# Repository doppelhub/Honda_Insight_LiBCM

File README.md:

# Honda_Insight_LiBCM
Replacement BCM for G1 Honda Insight Lithium Conversion
Licensed under Creative Commons - Attribution - ShareAlike 3.0
Project created and maintained by insightcentral.net user 'mudder' (a.k.a. John Sullivan).

<<<<<<< HEAD
LiBCM is a replacement computer that allows the G1 Honda Insight (2000-2006) to safely use modern lithium traction batteries.
=======
This is Natalya's fork repository for her branch on the LiBCM Project, which is created by insightcentral.net user 'mudder' (a.k.a. John Sullivan).
>>>>>>> f23abbbc6b13445ddd2d59ccdc4642e3edeb463f

LiBCM replaces the OEM Battery Control Module (BCM).  LiBCM is presently offered as two different 'Kits':
-'5AhG3 LiBCM Kit' uses 12S & 18S lithium battery modules from various modern Honda hybrids, or;
-'47Ah LiBCM Kit' uses 12S Samsung SDI lithium battery modules

<<<<<<< HEAD
While other lithium battery types are theoretically supported, integrating them with LiBCM is beyond the design goals for this project.  A few customers are using non-supported modules, but it requires custom BMS harnesses and also cell discharge curve characterization to create a Voc->SoC lookup table.

LiBCM officially supports the following lithium configurations:
-'5AhG3' - 48S ONLY, or;
-'47Ah'- either 48S or 60S.

NO OTHER CONFIGURATION is officially supported.  While the PCB's onboard BMS supports anywhere from 6S to 60S, you're on your own (firmware-wise) if you want to run anything besides 48S.  Future firmware updates might allow 54S and/or 60S support. 

See linsight.org for more information.
=======
LiBCM officially supports either 42S or 48S lithium configurations.  NO OTHER CONFIGURATION is officially supported.  While the PCB's onboard BMS supports anywhere from 6S to 60S - and also safely supports up to 84S using external modules (via an isoSPI interface), you're on your own (firmware-wise) if you want to run anything beyond 42S or 48S.
>>>>>>> f23abbbc6b13445ddd2d59ccdc4642e3edeb463f

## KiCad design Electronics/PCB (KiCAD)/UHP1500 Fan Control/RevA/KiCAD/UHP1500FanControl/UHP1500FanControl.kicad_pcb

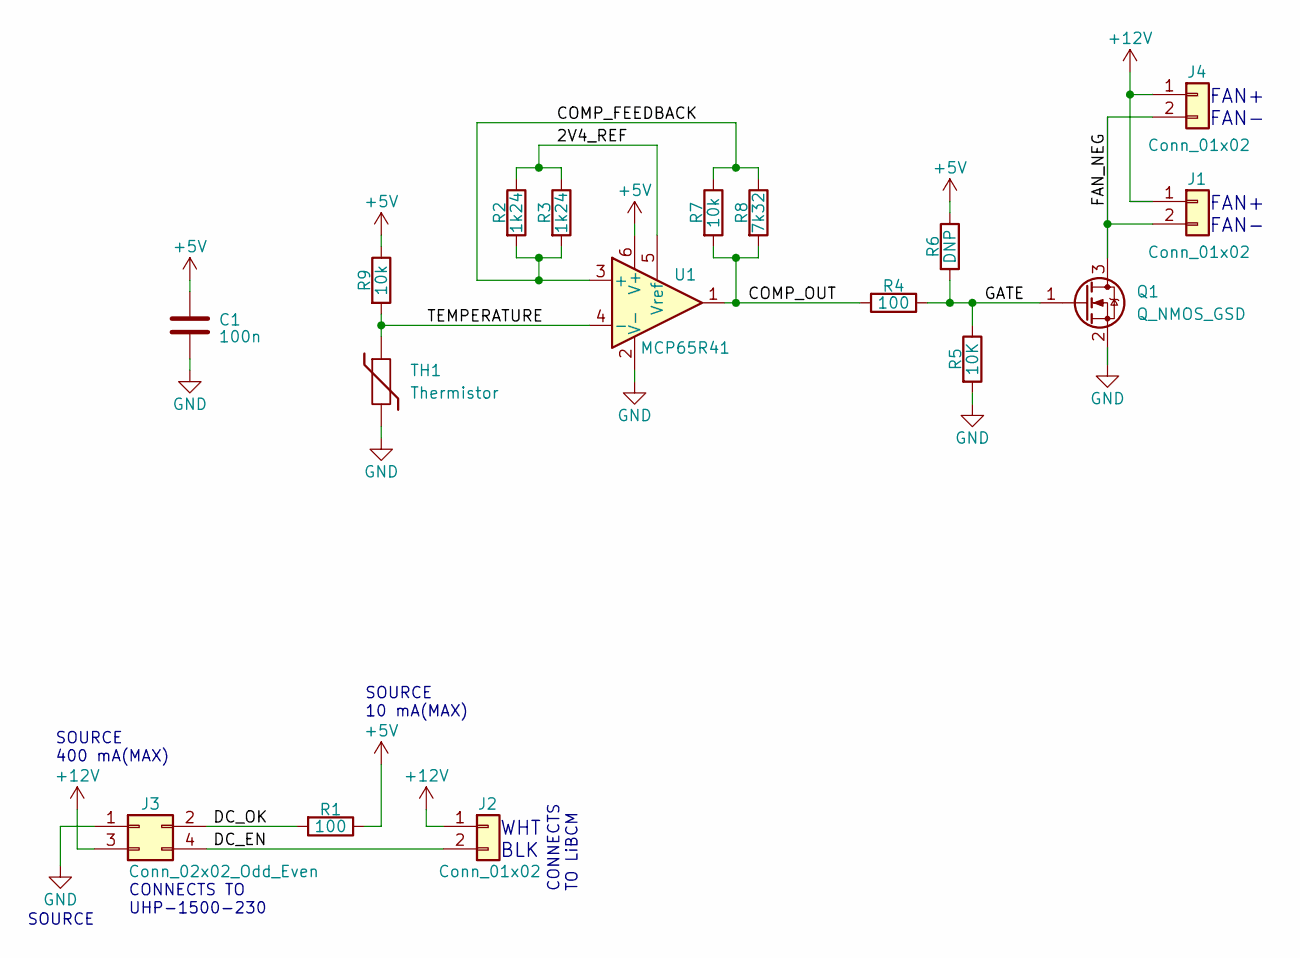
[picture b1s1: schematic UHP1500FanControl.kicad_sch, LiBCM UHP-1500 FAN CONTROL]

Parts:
C1: 100n; C_0805_2012Metric
J1, J2, J4: Conn_01x02; DIP-4_W8.89mm_SMDSocket_LongPads
J3: Conn_02x02_Odd_Even; PinHeader_2x02_P2.54mm_Vertical
Q1: Q_NMOS_GSD; SOT-23
R1, R4: 100; R_0805_2012Metric
R2, R3: 1k24; R_0805_2012Metric
R5: 10K; R_0805_2012Metric
R6: DNP; R_0805_2012Metric
R7, R9: 10k; R_0805_2012Metric
R8: 7k32; R_0805_2012Metric
TH1: Thermistor; R_0805_2012Metric
U1: MCP65R41; SOT-23-6

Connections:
+5V: C1.1, R1.1, R6.1, R9.1, U1.6 (V+)
+12V: J1.1, J2.1, J3.3, J4.1
/2V4_REF: R2.1, R3.1, U1.5 (Vref)
/COMP_FEEDBACK: R2.2, R3.2, R7.1, R8.1, U1.3 (+)
/COMP_OUT: R4.2, R7.2, R8.2, U1.1
/DC_EN: J2.2, J3.4
/DC_OK: J3.2, R1.2
/FAN_NEG: J1.2, J4.2, Q1.3 (D)
/GATE: Q1.1 (G), R4.1, R5.1, R6.2
/TEMPERATURE: R9.2, TH1.1, U1.4 (-)
GND: C1.2, J3.1, Q1.2 (S), R5.2, TH1.2, U1.2 (V-)

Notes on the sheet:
SOURCE 10 mA(MAX)
FAN+ FAN-
WHT BLK
CONNECTS TO LiBCM
SOURCE
CONNECTS TO UHP-1500-230
SOURCE 400 mA(MAX)

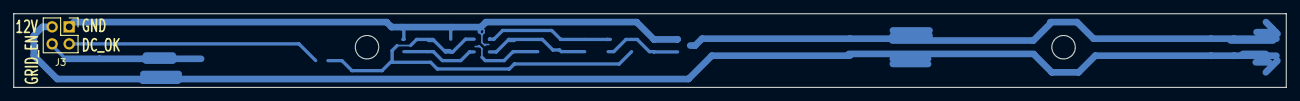
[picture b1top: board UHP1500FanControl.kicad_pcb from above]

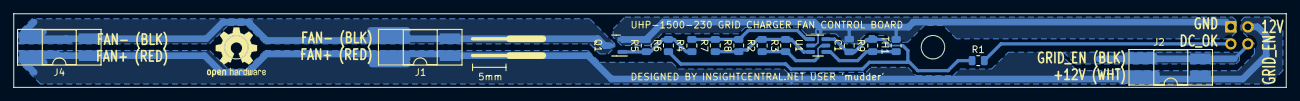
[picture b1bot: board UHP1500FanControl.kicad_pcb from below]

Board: 2 copper layers, 190.0 x 11.0 mm, 17 parts (16 on the bottom side), 11 nets.

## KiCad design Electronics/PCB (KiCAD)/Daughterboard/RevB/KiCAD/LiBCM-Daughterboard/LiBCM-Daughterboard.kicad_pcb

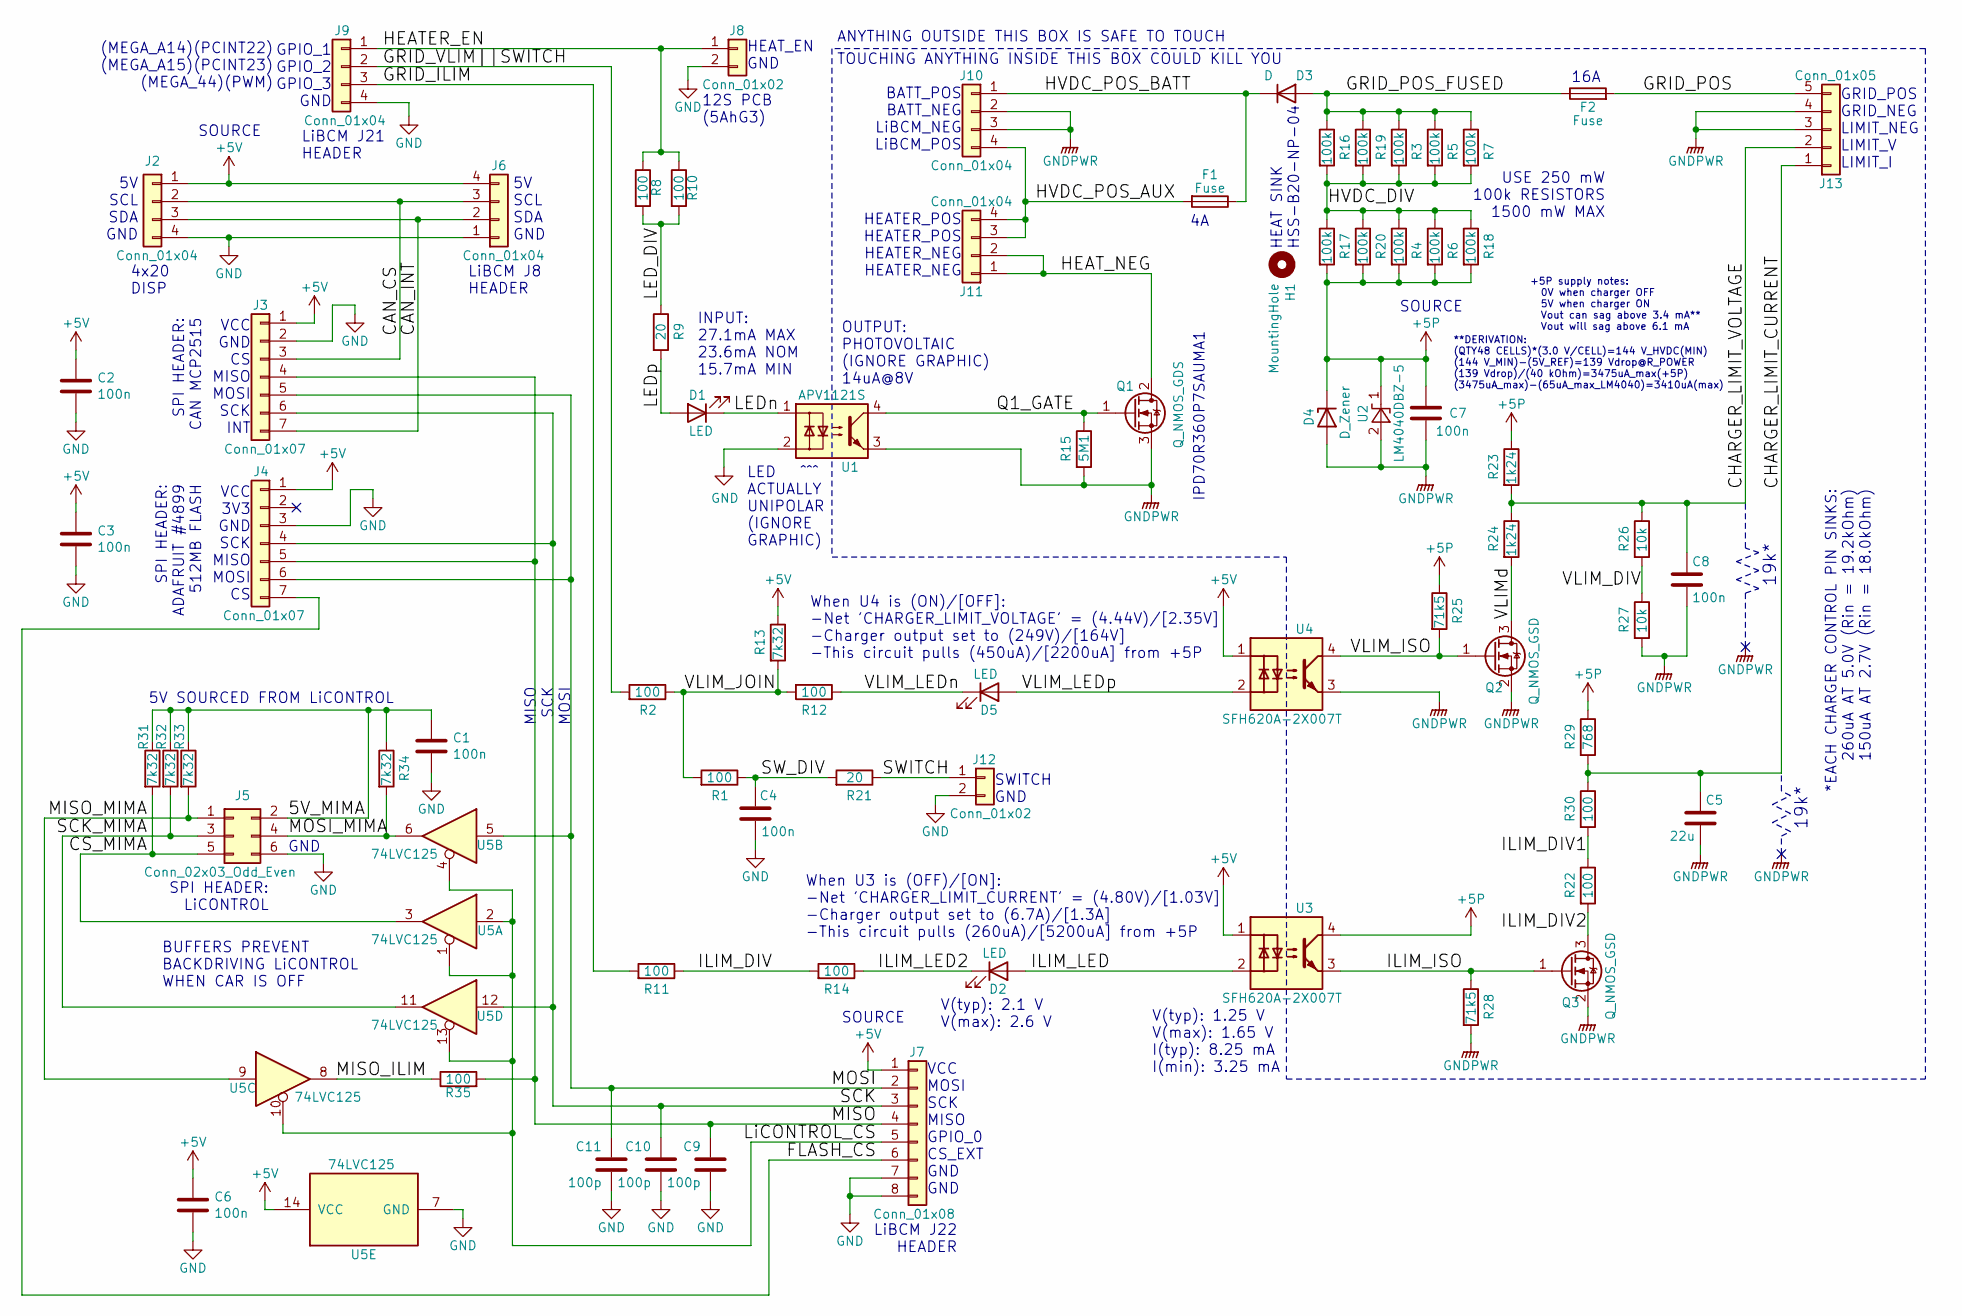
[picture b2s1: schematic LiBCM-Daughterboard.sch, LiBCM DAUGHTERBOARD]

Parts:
C1, C2, C3, C4, C6, C7, C8: 100n; C_0805_2012Metric
C5: 22u; C_1210_3225Metric
C9, C10, C11: 100p; C_0805_2012Metric
D1, D2, D5: LED; LED_0805_2012Metric
D3: D; TO-220-2_Horizontal_TabDown
D4: D_Zener; D_SOD-123
F1, F2: Fuse; Fuseholder_Cylinder-5x20mm_Schurter_0031_8201_Horizontal_Op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
H1: MountingHole; MountingHole_3.2mm_M3
J2, J6, J9: Conn_01x04; PinHeader_1x04_P2.54mm_Vertical
J3, J4: Conn_01x07; PinHeader_1x07_P2.54mm_Vertical
J5: Conn_02x03_Odd_Even; PinHeader_2x03_P2.54mm_Vertical
J7: Conn_01x08; PinHeader_1x08_P2.54mm_Vertical
J8, J12: Conn_01x02; PinHeader_1x02_P2.54mm_Vertical
J10, J11: Conn_01x04; PhoenixContact_MCV_1,5_4-G-3.5_1x04_P3.50mm_Vertical
J13: Conn_01x05; PhoenixContact_MCV_1,5_5-G-3.5_1x05_P3.50mm_Vertical
Q1: Q_NMOS_GDS; TO-252-3_TabPin2
Q2, Q3: Q_NMOS_GSD; SOT-23
R1, R2, R8, R10, R11, R12, R14, R22, R30, R35: 100; R_0805_2012Metric
R3, R4, R5, R6, R7, R16, R17, R18, R19, R20: 100k; R_0805_2012Metric
R9, R21: 20; R_0805_2012Metric
R13, R31, R32, R33, R34: 7k32; R_0805_2012Metric
R15: 5M1; R_1206_3216Metric
R23, R24: 1k24; R_0805_2012Metric
R25, R28: 71k5; R_0805_2012Metric
R26, R27: 10k; R_0805_2012Metric
R29: 768; R_0805_2012Metric
U1: APV1121S; SOP-4_3.8x4.1mm_P2.54mm
U2: LM4040DBZ-5; SOT-23
U3, U4: SFH620A-2X007T; SMDIP-4_W9.53mm_Clearance8mm
U5: 74LVC125; SO-14_3.9x8.65mm_P1.27mm

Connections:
+5P: C7.1, D4.1 (K), R4.2, R6.2, R17.2, R18.2, R20.2, R23.1, R25.1, R29.1, U2.1 (K), U3.4
+5V: C2.1, C3.1, C6.1, J2.1, J3.1, J4.1, J6.4, J7.1, R13.1, U3.1, U4.1, U5.14 (VCC)
/5V_MIMA: C1.1, J5.2, R31.1, R32.1, R33.1, R34.1
/CAN_CS: J2.2, J3.3, J6.3
/CAN_INT: J2.3, J3.7, J6.2
/CHARGER_LIMIT_CURRENT: C5.1, J13.1, R29.2, R30.1
/CHARGER_LIMIT_VOLTAGE: C8.1, J13.2, R23.2, R24.1, R26.1
/CS_MIMA: J5.5, R31.2, U5.3
/FLASH_CS: J4.7, J7.6
/GRID_ILIM: J9.3, R11.2
/GRID_POS: F2.2, J13.5
/GRID_POS_FUSED: D3.2 (A), F2.1, R3.1, R5.1, R7.1, R16.1, R19.1
/GRID_VLIM||SWITCH: J9.2, R2.2
/HEATER_EN: J8.1, J9.1, R8.1, R10.1
/HEAT_NEG: J11.1, J11.2, Q1.2 (D)
/HVDC_DIV: R3.2, R4.1, R5.2, R6.1, R7.2, R16.2, R17.1, R18.1, R19.2, R20.1
/HVDC_POS_AUX: F1.2, J10.4, J11.3, J11.4
/HVDC_POS_BATT: D3.1 (K), F1.1, J10.1
/ILIM_DIV1: R22.1, R30.2
/ILIM_DIV2: Q3.3 (D), R22.2
/ILIM_ISO: Q3.1 (G), R28.1, U3.3
/ILIM_LED_1: R11.1, R14.2
/ILIM_LED_2: D2.1 (K), R14.1; also elsewhere on the board
/ILIM_LED_3: D2.2 (A), U3.2; also elsewhere on the board
/LED_DIV: R8.2, R9.1, R10.2
/LEDn: D1.1 (K), U1.1
/LEDp: D1.2 (A), R9.2
/LiCONTROL_CS: J7.5, U5.1, U5.2, U5.4, U5.10, U5.13
/MISO: C9.1, J3.4, J4.5, J7.4, R35.2
/MISO_ILIM: R35.1, U5.8
/MISO_MIMA: J5.1, R33.2, U5.9
/MOSI: C11.1, J3.5, J4.6, J7.2, U5.5
/MOSI_MIMA: J5.4, R34.2, U5.6
/Q1_GATE: Q1.1 (G), R15.1, U1.4
/SCK: C10.1, J3.6, J4.4, J7.3, U5.12
/SCK_MIMA: J5.3, R32.2, U5.11
/SWITCH: J12.1, R21.1
/SW_DIV: C4.1, R1.1, R21.2
/VLIM_DIV: R26.2, R27.1
/VLIM_ISO: Q2.1 (G), R25.2, U4.4
/VLIM_JOIN: R1.2, R2.1, R12.2, R13.2
/VLIM_LEDn: D5.1 (K), R12.1
/VLIM_LEDp: D5.2 (A), U4.2
/VLIMd: Q2.3 (D), R24.2
GND: C1.2, C2.2, C3.2, C4.2, C6.2, C9.2, C10.2, C11.2, J2.4, J3.2, J4.3, J5.6, J6.1, J7.7, J7.8, J8.2, J9.4, J12.2, U1.2, U5.7 (GND)
GNDPWR: C5.2, C7.2, C8.2, D4.2 (A), J10.2, J10.3, J13.3, J13.4, Q1.3 (S), Q2.2 (S), Q3.2 (S), R15.2, R27.2, R28.2, U1.3, U2.2 (A), U4.3

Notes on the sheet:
GPIO_1 GPIO_2 GPIO_3 GND
SPI HEADER: CAN MCP2515
OUTPUT: PHOTOVOLTAIC (IGNORE GRAPHIC) 14uA@8V
LED ^^^ ACTUALLY UNIPOLAR (IGNORE GRAPHIC)
IPD70R360P7SAUMA1
LiBCM J21 HEADER
HEATER_POS HEATER_POS HEATER_NEG HEATER_NEG
(MEGA_A14)(PCINT22) (MEGA_A15)(PCINT23) (MEGA_44)(PWM)
SPI HEADER: ADAFRUIT #4899 512MB FLASH
VCC 3V3 GND SCK MISO MOSI CS
VCC GND CS MISO MOSI SCK INT
LiBCM J22 HEADER
VCC MOSI SCK MISO GPIO_0 CS_EXT GND GND
16A
*EACH CHARGER CONTROL PIN SINKS: 260uA AT 5.0V (Rin = 19.2kOhm) 150uA AT 2.7V (Rin = 18.0kOhm)
GRID_POS GRID_NEG LIMIT_NEG LIMIT_V LIMIT_I
BATT_POS BATT_NEG LiBCM_NEG LiBCM_POS
TOUCHING ANYTHING INSIDE THIS BOX COULD KILL YOU
ANYTHING OUTSIDE THIS BOX IS SAFE TO TOUCH
INPUT: 27.1mA MAX 23.6mA NOM 15.7mA MIN
5V SCL SDA GND
LiBCM J8 HEADER
4x20 DISP
HEAT SINK HSS-B20-NP-04
SOURCE
V(typ): 2.1 V V(max): 2.6 V
V(typ): 1.25 V V(max): 1.65 V I(typ): 8.25 mA I(min): 3.25 mA
SPI HEADER: LiCONTROL
MISO SCK MOSI
12S PCB (5AhG3)
HEAT_EN GND
19k*
When U4 is (ON)/[OFF]: -Net 'CHARGER_LIMIT_VOLTAGE' = (4.44V)/[2.35V] -Charger output set to (249V)/[164V] -This circuit pulls (450uA)/[2200uA] from +5P
SWITCH GND
When U3 is (OFF)/[ON]: -Net 'CHARGER_LIMIT_CURRENT' = (4.80V)/[1.03V] -Charger output set to (6.7A)/[1.3A] -This circuit pulls (260uA)/[5200uA] from +5P
USE 250 mW 100k RESISTORS 1500 mW MAX
+5P supply notes: 0V when charger OFF 5V when charger ON Vout can sag above 3.4 mA** Vout will sag above 6.1 mA
**DERIVATION: (QTY48 CELLS)*(3.0 V/CELL)=144 V_HVDC(MIN) (144 V_MIN)-(5V_REF)=139 Vdrop@R_POWER (139 Vdrop)/(40 kOhm)=3475uA_max(+5P) (3475uA_max)-(65uA_max_LM4040)=3410uA(max)
GND
BUFFERS PREVENT BACKDRIVING LiCONTROL WHEN CAR IS OFF

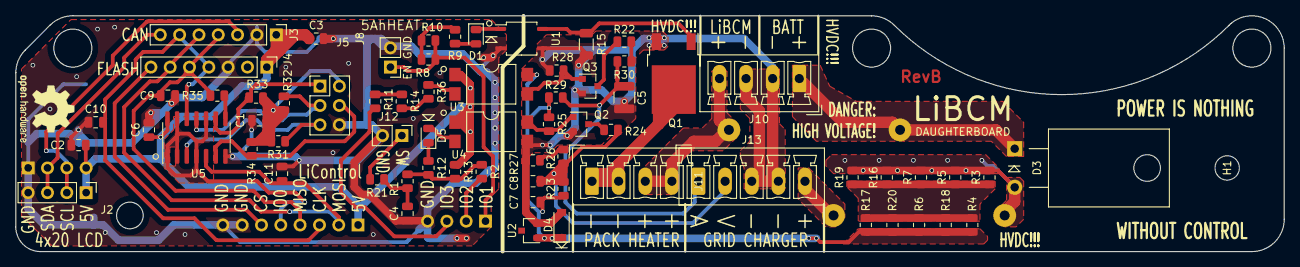
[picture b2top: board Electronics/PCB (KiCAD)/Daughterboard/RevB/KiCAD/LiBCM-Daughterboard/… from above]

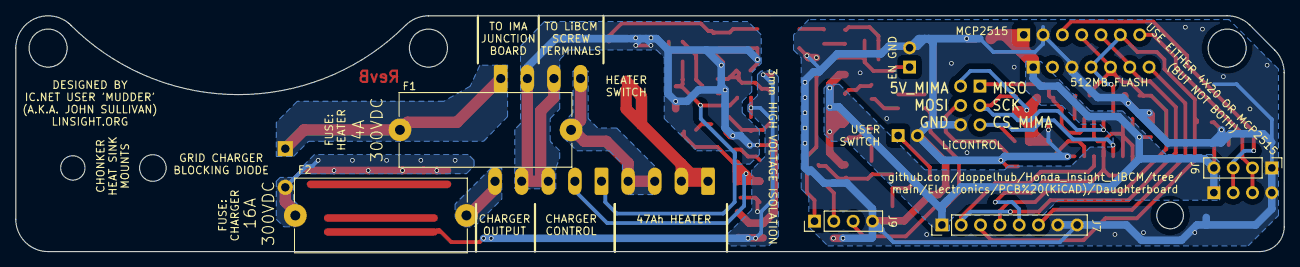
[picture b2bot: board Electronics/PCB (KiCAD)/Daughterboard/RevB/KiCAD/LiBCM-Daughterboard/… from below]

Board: 4 copper layers, 166.8 x 31.0 mm, 74 parts (5 on the bottom side), 46 nets.

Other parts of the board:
R36: 100; R_0805_2012Metric

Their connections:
/ILIM_LED_2: R36.2; also elsewhere on the board
/ILIM_LED_3: R36.1; also elsewhere on the board

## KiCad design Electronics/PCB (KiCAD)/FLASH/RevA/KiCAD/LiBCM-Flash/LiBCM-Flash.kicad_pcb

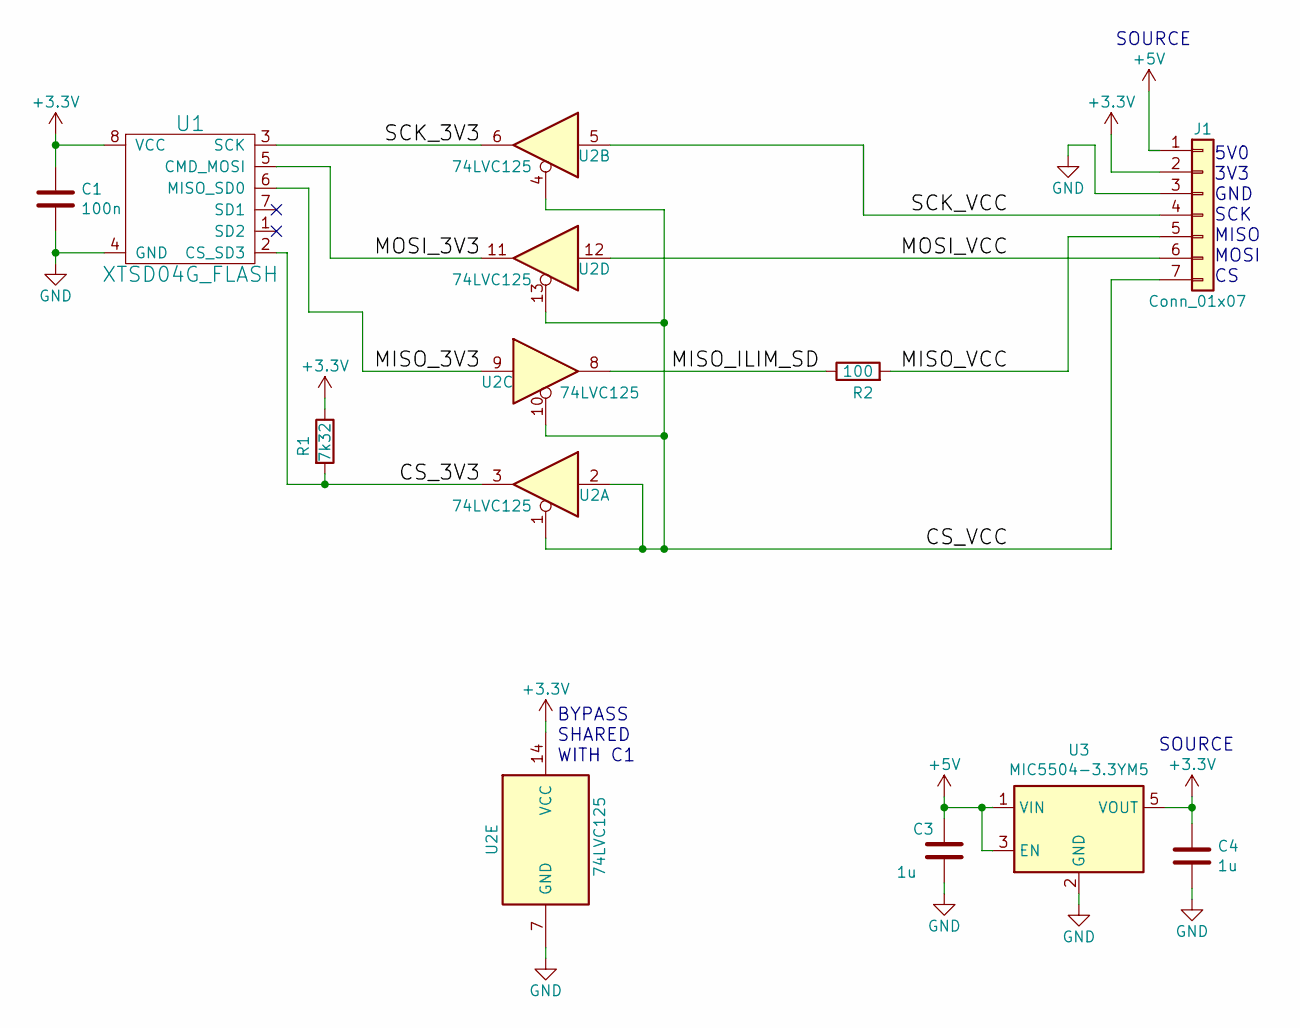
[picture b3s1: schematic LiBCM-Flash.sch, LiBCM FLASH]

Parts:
C1: 100n; C_0805_2012Metric
C3, C4: 1u; C_0805_2012Metric
J1: Conn_01x07; PinHeader_1x07_P2.54mm_Vertical
R1: 7k32; R_0805_2012Metric
R2: 100; R_0805_2012Metric
U1: XTSD04G_FLASH; NXP_LGA-8_3x5mm_P1.25mm_H1.2mm
U2: 74LVC125; SO-14_3.9x8.65mm_P1.27mm
U3: MIC5504-3.3YM5; SOT-23-5

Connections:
+3V3: C1.1, C4.1, J1.2, R1.1, U1.8 (VCC), U2.14 (VCC), U3.5 (VOUT)
+5V: C3.1, J1.1, U3.1 (VIN), U3.3 (EN)
/CS_3V3: R1.2, U1.2 (CS_SD3), U2.3
/CS_VCC: J1.7, U2.1, U2.2, U2.4, U2.10, U2.13
/MISO_3V3: U1.6 (MISO_SD0), U2.9
/MISO_ILIM_SD: R2.1, U2.8
/MISO_VCC: J1.5, R2.2
/MOSI_3V3: U1.5 (CMD_MOSI), U2.11
/MOSI_VCC: J1.6, U2.12
/SCK_3V3: U1.3 (SCK), U2.6
/SCK_VCC: J1.4, U2.5
GND: C1.2, C3.2, C4.2, J1.3, U1.4 (GND), U2.7 (GND), U3.2 (GND)

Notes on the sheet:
SOURCE
5V0 3V3 GND SCK MISO MOSI CS
BYPASS SHARED WITH C1

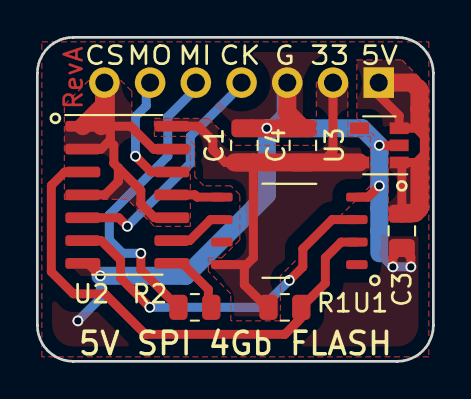
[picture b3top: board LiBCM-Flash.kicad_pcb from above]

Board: 4 copper layers, 22.0 x 18.0 mm, 9 parts (1 on the bottom side), 12 nets.

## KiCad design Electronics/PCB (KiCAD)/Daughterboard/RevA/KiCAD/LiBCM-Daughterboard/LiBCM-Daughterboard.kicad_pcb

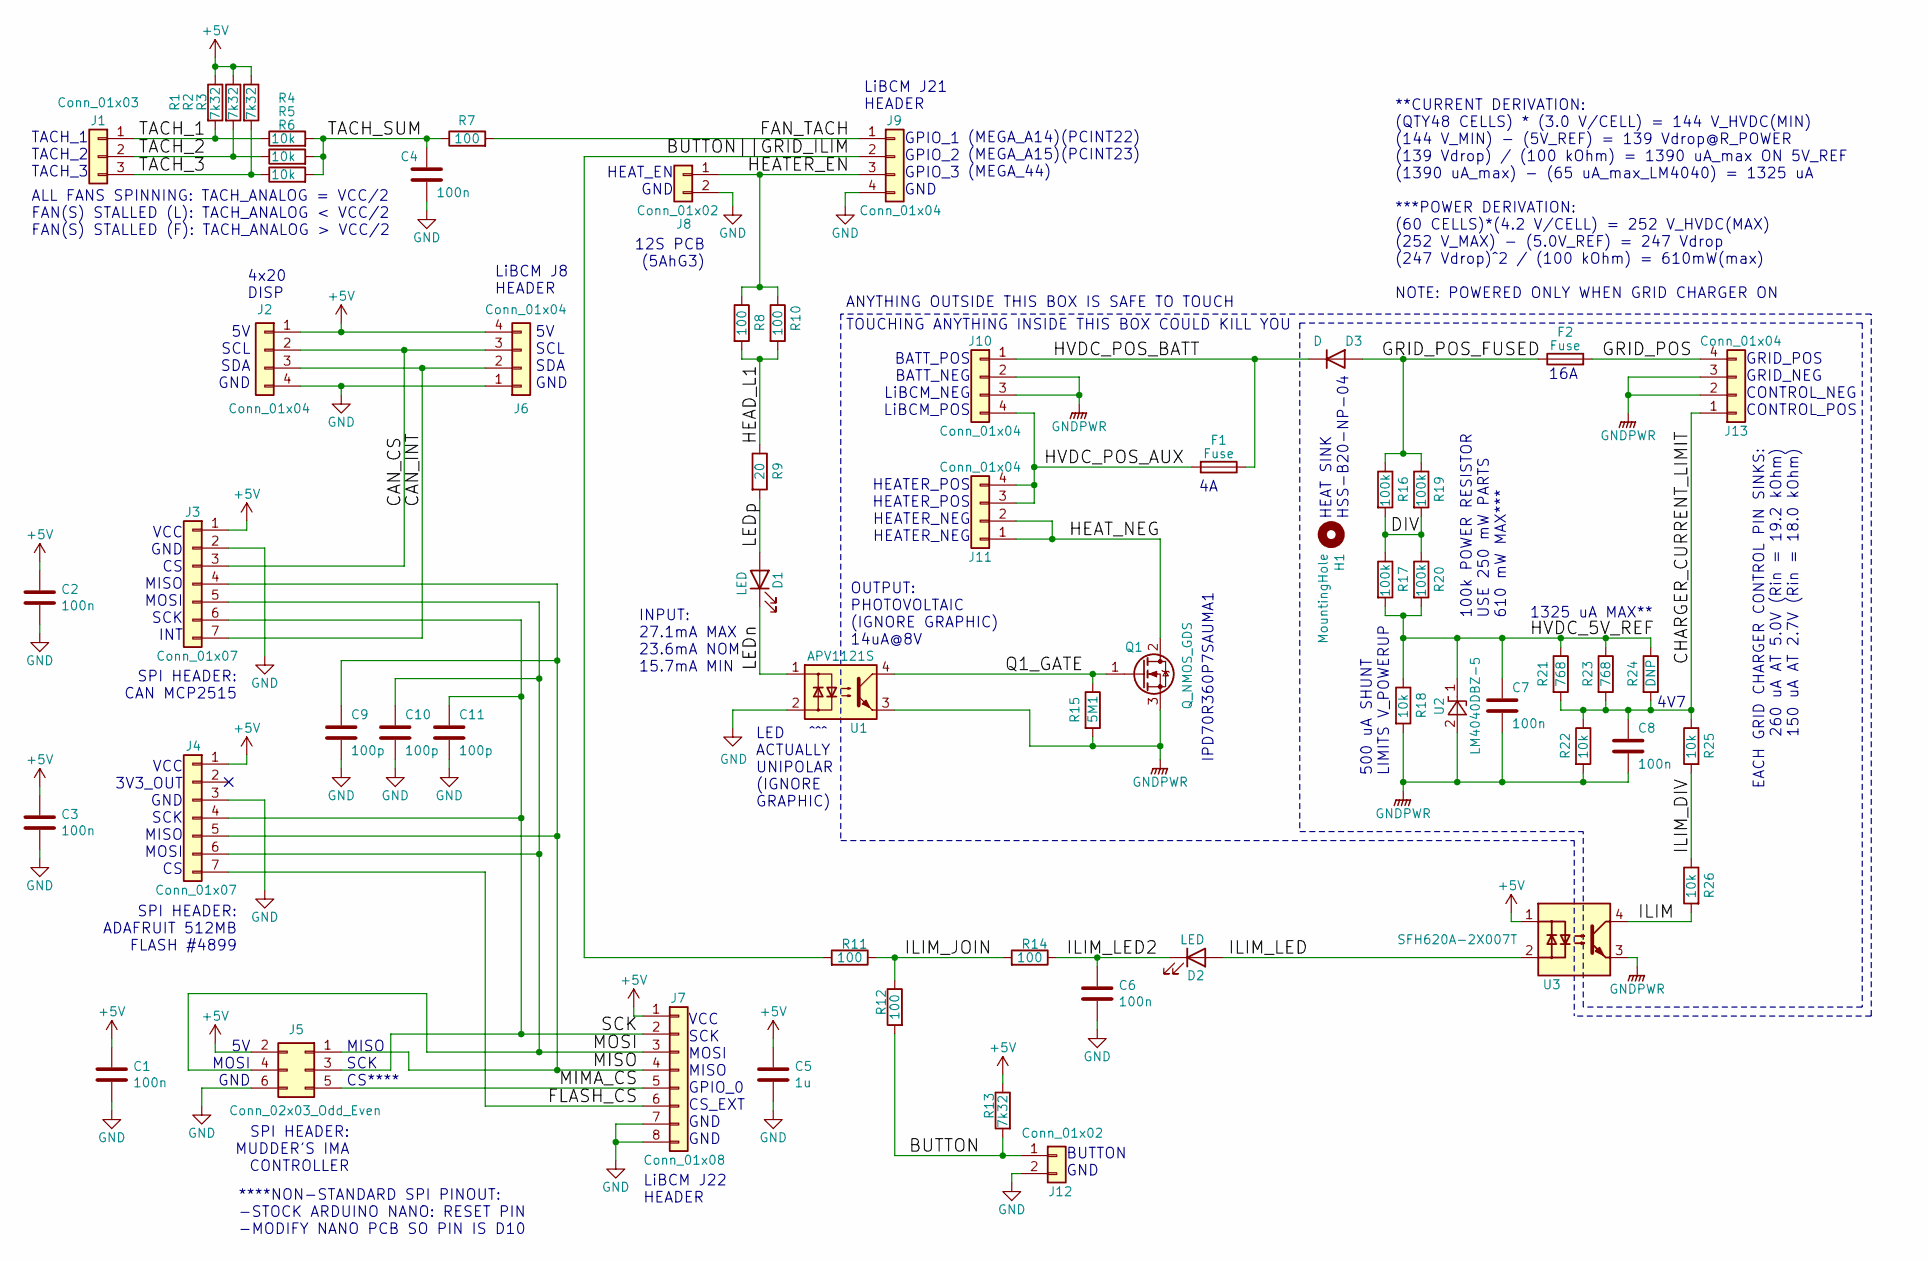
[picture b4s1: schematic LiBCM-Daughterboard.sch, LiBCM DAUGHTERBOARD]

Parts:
C1, C2, C3, C4, C6, C7, C8: 100n; C_0805_2012Metric
C5: 1u; C_0805_2012Metric
C9, C10, C11: 100p; C_0805_2012Metric
D1, D2: LED; LED_0805_2012Metric
D3: D; TO-220-2_Horizontal_TabDown
F1, F2: Fuse; Fuseholder_Cylinder-5x20mm_Schurter_0031_8201_Horizontal_Op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
H1: MountingHole; MountingHole_3.2mm_M3
J1: Conn_01x03; PhoenixContact_MCV_1,5_3-G-3.5_1x03_P3.50mm_Vertical
J2, J6, J9: Conn_01x04; PinHeader_1x04_P2.54mm_Vertical
J3, J4: Conn_01x07; PinHeader_1x07_P2.54mm_Vertical
J5: Conn_02x03_Odd_Even; PinHeader_2x03_P2.54mm_Vertical
J7: Conn_01x08; PinHeader_1x08_P2.54mm_Vertical
J8, J12: Conn_01x02; PinHeader_1x02_P2.54mm_Vertical
J10, J11, J13: Conn_01x04; PhoenixContact_MCV_1,5_4-G-3.5_1x04_P3.50mm_Vertical
Q1: Q_NMOS_GDS; TO-252-3_TabPin2
R1, R2, R3, R13: 7k32; R_0805_2012Metric
R4, R5, R6, R18, R22, R25, R26: 10k; R_0805_2012Metric
R7, R8, R10, R11, R12, R14: 100; R_0805_2012Metric
R9: 20; R_0805_2012Metric
R15: 5M1; R_1206_3216Metric
R16, R17, R19, R20: 100k; R_0805_2012Metric
R21, R23: 768; R_0805_2012Metric
R24: DNP; R_0805_2012Metric
U1: APV1121S; SOP-4_4.4x2.6mm_P1.27mm
U2: LM4040DBZ-5; SOT-23
U3: SFH620A-2X007T; SMDIP-4_W9.53mm_Clearance8mm

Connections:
+5V: C1.1, C2.1, C3.1, C5.1, J2.1, J3.1, J4.1, J5.2, J6.4, J7.1, R1.1, R2.1, R3.1, R13.1, U3.1
/BUTTON: J12.1, R12.2, R13.2
/BUTTON||GRID_ILIM: J9.2, R11.2
/CAN_CS: J2.2, J3.3, J6.3
/CAN_INT: J2.3, J3.7, J6.2
/CHARGER_CURRENT_LIMIT: C8.1, J13.1, R21.2, R22.1, R23.2, R24.2, R25.1
/DIV: R16.2, R17.1, R19.2, R20.1
/FAN_TACH: J9.1, R7.2
/FLASH_CS: J4.7, J7.6
/GRID_POS: F2.2, J13.4
/GRID_POS_FUSED: D3.2 (A), F2.1, R16.1, R19.1
/HEAD_L1: R8.2, R9.1, R10.2
/HEATER_EN: J8.1, J9.3, R8.1, R10.1
/HEAT_NEG: J11.1, J11.2, Q1.2 (D)
/HVDC_5V_REF: C7.1, R17.2, R18.1, R20.2, R21.1, R23.1, R24.1, U2.1 (K)
/HVDC_POS_AUX: F1.2, J10.4, J11.3, J11.4
/HVDC_POS_BATT: D3.1 (K), F1.1, J10.1
/ILIM: R26.2, U3.4
/ILIM_DIV: R25.2, R26.1
/ILIM_JOIN: R11.1, R12.1, R14.2
/ILIM_LED: D2.2 (A), U3.2
/ILIM_LED2: C6.1, D2.1 (K), R14.1
/LEDn: D1.1 (K), U1.1
/LEDp: D1.2 (A), R9.2
/MIMA_CS: J5.5, J7.5
/MISO: C9.1, J3.4, J4.5, J5.1, J7.4
/MOSI: C10.1, J3.5, J4.6, J5.4, J7.3
/Q1_GATE: Q1.1 (G), R15.1, U1.4
/SCK: C11.1, J3.6, J4.4, J5.3, J7.2
/TACH_1: J1.1, R1.2, R4.1
/TACH_2: J1.2, R2.2, R5.1
/TACH_3: J1.3, R3.2, R6.1
/TACH_SUM: C4.1, R4.2, R5.2, R6.2, R7.1
GND: C1.2, C2.2, C3.2, C4.2, C5.2, C6.2, C9.2, C10.2, C11.2, J2.4, J3.2, J4.3, J5.6, J6.1, J7.7, J7.8, J8.2, J9.4, J12.2, U1.2
GNDPWR: C7.2, C8.2, J10.2, J10.3, J13.2, J13.3, Q1.3 (S), R15.2, R18.2, R22.2, U1.3, U2.2 (A), U3.3

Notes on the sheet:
GPIO_1 GPIO_2 GPIO_3 GND
TACH_1 TACH_2 TACH_3
SPI HEADER: CAN MCP2515
OUTPUT: PHOTOVOLTAIC (IGNORE GRAPHIC) 14uA@8V
LED ^^^ ACTUALLY UNIPOLAR (IGNORE GRAPHIC)
IPD70R360P7SAUMA1
HEAT_EN GND
LiBCM J21 HEADER
SPI HEADER: MUDDER'S IMA CONTROLLER
HEATER_POS HEATER_POS HEATER_NEG HEATER_NEG
ALL FANS SPINNING: TACH_ANALOG = VCC/2 FAN(S) STALLED (L): TACH_ANALOG < VCC/2 FAN(S) STALLED (F): TACH_ANALOG > VCC/2
(MEGA_A14)(PCINT22) (MEGA_A15)(PCINT23) (MEGA_44)
SPI HEADER: ADAFRUIT 512MB FLASH #4899
VCC 3V3_OUT GND SCK MISO MOSI CS
VCC GND CS MISO MOSI SCK INT
LiBCM J22 HEADER
VCC SCK MOSI MISO GPIO_0 CS_EXT GND GND
12S PCB (5AhG3)
16A
EACH GRID CHARGER CONTROL PIN SINKS: 260 uA AT 5.0V (Rin = 19.2 kOhm) 150 uA AT 2.7V (Rin = 18.0 kOhm)
1325 uA MAX**
100k POWER RESISTOR USE 250 mW PARTS 610 mW MAX***
**CURRENT DERIVATION: (QTY48 CELLS) * (3.0 V/CELL) = 144 V_HVDC(MIN) (144 V_MIN) - (5V_REF) = 139 Vdrop@R_POWER (139 Vdrop) / (100 kOhm) = 1390 uA_max ON 5V_REF (1390 uA_max) - (65 uA_max_LM4040) = 1325 uA ***POWER DERIVATION: (60 CELLS)*(4.2 V/CELL) = 252 V_HVDC(MAX) (252 V_MAX) - (5.0V_REF) = 247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
4V7
500 uA SHUNT LIMITS V_POWERUP
GRID_POS GRID_NEG CONTROL_NEG CONTROL_POS
BATT_POS BATT_NEG LiBCM_NEG LiBCM_POS
TOUCHING ANYTHING INSIDE THIS BOX COULD KILL YOU
ANYTHING OUTSIDE THIS BOX IS SAFE TO TOUCH
MISO SCK CS****
5V MOSI GND
****NON-STANDARD SPI PINOUT: -STOCK ARDUINO NANO: RESET PIN -MODIFY NANO PCB SO PIN IS D10
INPUT: 27.1mA MAX 23.6mA NOM 15.7mA MIN
BUTTON GND
5V SCL SDA GND
LiBCM J8 HEADER
4x20 DISP
HEAT SINK HSS-B20-NP-04

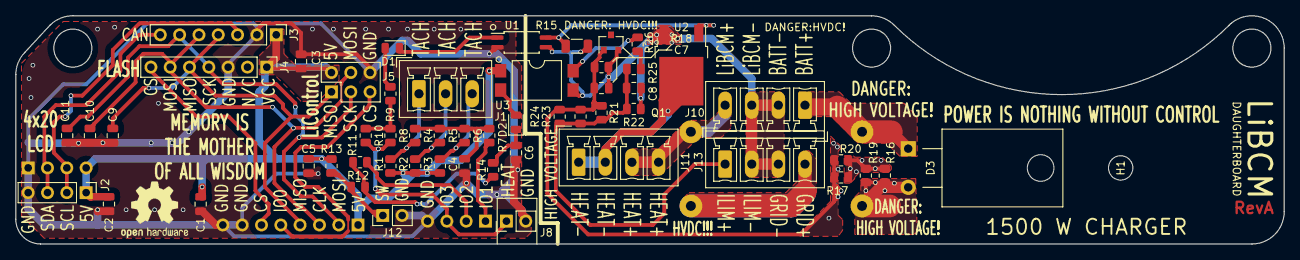
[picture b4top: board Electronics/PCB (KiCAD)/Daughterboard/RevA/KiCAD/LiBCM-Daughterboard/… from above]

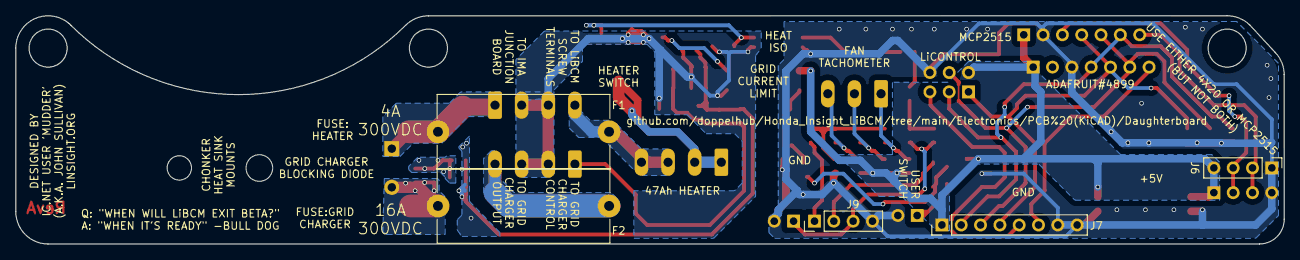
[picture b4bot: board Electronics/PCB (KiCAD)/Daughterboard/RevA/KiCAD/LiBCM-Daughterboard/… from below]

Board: 4 copper layers, 166.8 x 30.0 mm, 60 parts (5 on the bottom side), 35 nets.

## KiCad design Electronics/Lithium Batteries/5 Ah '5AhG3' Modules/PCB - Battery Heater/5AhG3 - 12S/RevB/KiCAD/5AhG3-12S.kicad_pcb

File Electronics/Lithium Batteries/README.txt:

Long term cycle test data located here:
https://github.com/doppelhub/Long-Term-Lithium-Cell-Tests

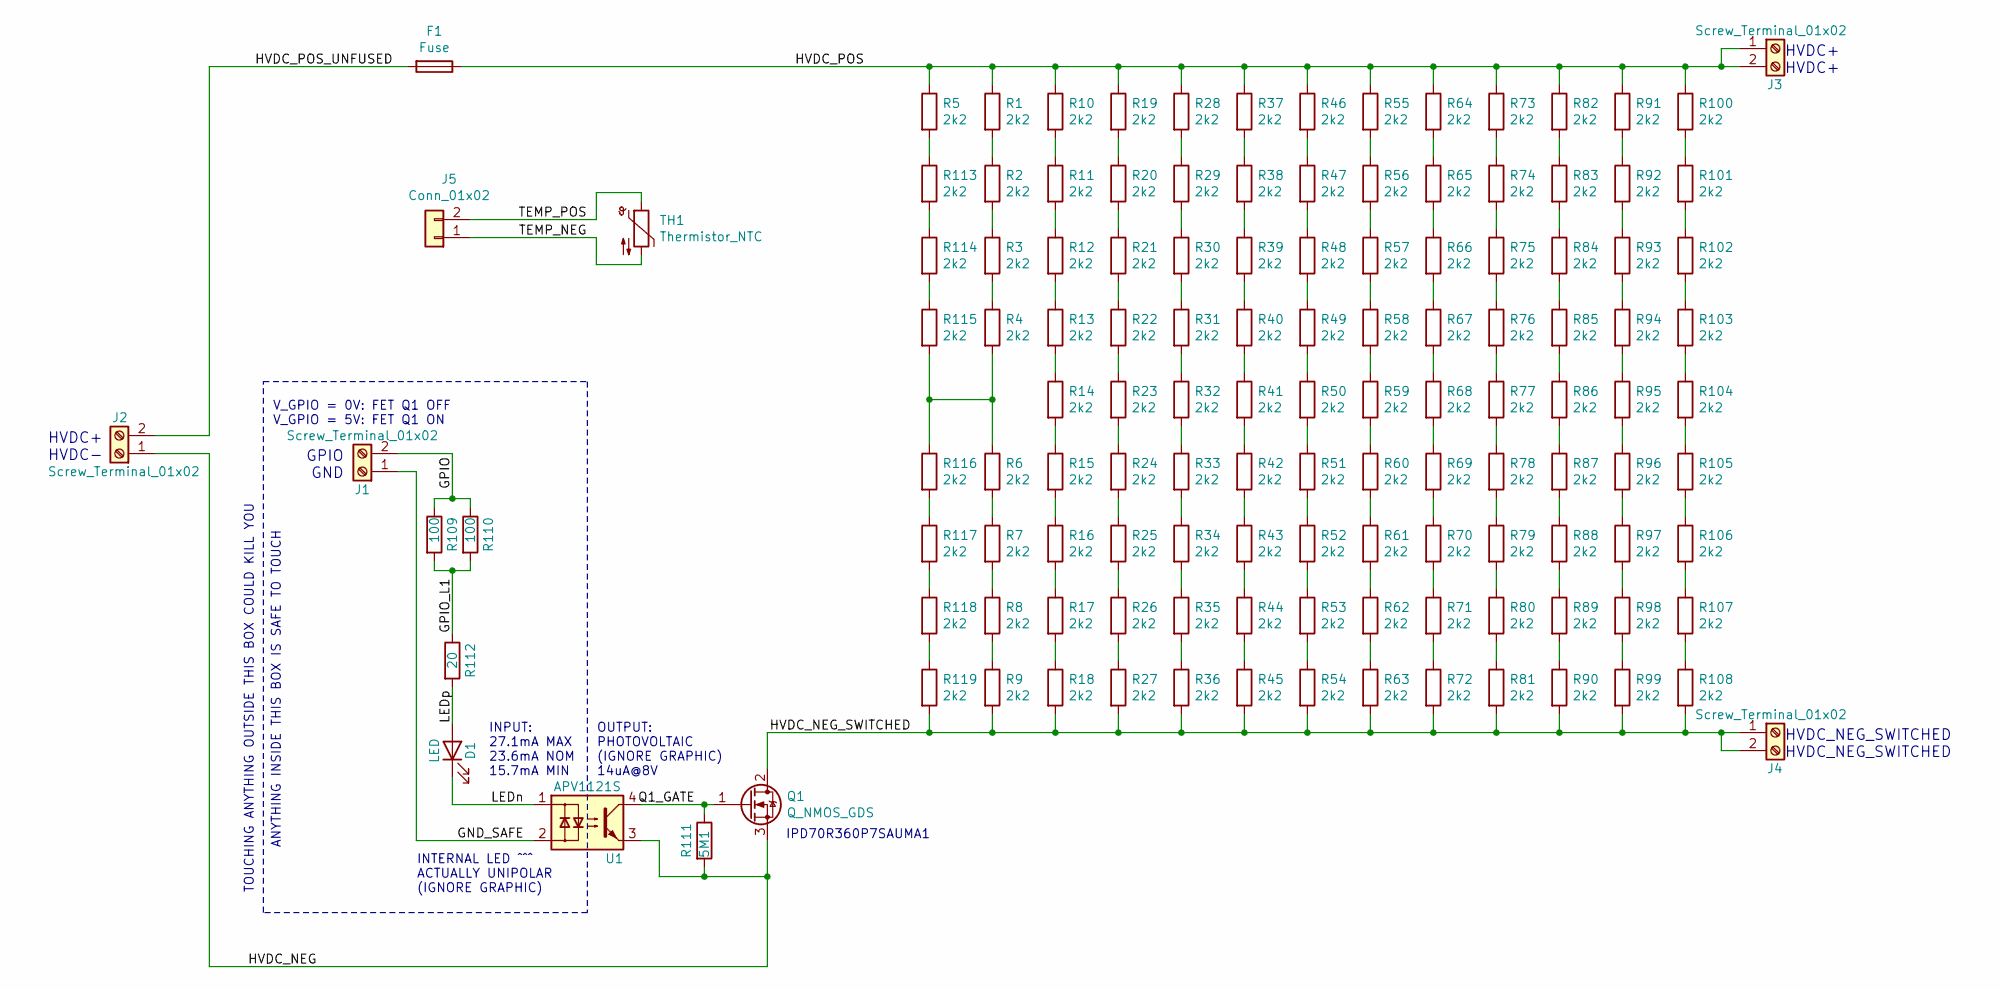
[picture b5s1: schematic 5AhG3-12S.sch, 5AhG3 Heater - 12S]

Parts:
D1: LED; LED_0805_2012Metric
F1: Fuse; Fuseholder_Cylinder-5x20mm_Schurter_0031_8201_Horizontal_Op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
J1: Screw_Terminal_01x02; PinHeader_1x02_P2.54mm_Vertical
J2, J3, J4: Screw_Terminal_01x02; PhoenixContact_MCV_1,5_2-G-3.5_1x02_P3.50mm_Vertical
J5: Conn_01x02; PinHeader_1x02_P2.54mm_Vertical
Q1: Q_NMOS_GDS; TO-252-3_TabPin2
R1, R2, R3, R4, R5, R6, R7, R8, R9, R10, R11, R12, R13, R14, R15, R16, R17, R18, R19, R20, R21, R22, R23, R24, R25, R26, R27, R28, R29, R30, R31, R32, R33, R34, R35, R36, R37, R38, R39, R40, R41, R42, R43, R44, R45, R46, R47, R48, R49, R50, R51, R52, R53, R54, R55, R56, R57, R58, R59, R60, R61, R62, R63, R64, R65, R66, R67, R68, R69, R70, R71, R72, R73, R74, R75, R76, R77, R78, R79, R80, R81, R82, R83, R84, R85, R86, R87, R88, R89, R90, R91, R92, R93, R94, R95, R96, R97, R98, R99, R100, R101, R102, R103, R104, R105, R106, R107, R108, R113, R114, R115, R116, R117, R118, R119: 2k2; R_2010_5025Metric
R109, R110: 100; R_0805_2012Metric
R111: 5M1; R_1206_3216Metric
R112: 20; R_0805_2012Metric
TH1: Thermistor_NTC; R_0805_2012Metric
U1: APV1121S; SOP-4_3.8x4.1mm_P2.54mm

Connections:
/GND_SAFE: J1.1, U1.2
/GPIO: J1.2, R109.1, R110.1
/GPIO_L1: R109.2, R110.2, R112.1
/HVDC_NEG: J2.1, Q1.3 (S), R111.2, U1.3
/HVDC_NEG_SWITCHED: J4.1, J4.2, Q1.2 (D), R9.2, R18.2, R27.2, R36.2, R45.2, R54.2, R63.2, R72.2, R81.2, R90.2, R99.2, R108.2, R119.2
/HVDC_POS: F1.1, J3.1, J3.2, R1.1, R5.1, R10.1, R19.1, R28.1, R37.1, R46.1, R55.1, R64.1, R73.1, R82.1, R91.1, R100.1
/HVDC_POS_UNFUSED: F1.2, J2.2
/LEDn: D1.1 (K), U1.1
/LEDp: D1.2 (A), R112.2
/Q1_GATE: Q1.1 (G), R111.1, U1.4
/TEMP_NEG: J5.1, TH1.2
/TEMP_POS: J5.2, TH1.1
unnamed: R1.2, R2.1
unnamed: R2.2, R3.1
unnamed: R3.2, R4.1
unnamed: R6.2, R7.1
unnamed: R7.2, R8.1
unnamed: R8.2, R9.1
unnamed: R10.2, R11.1
unnamed: R11.2, R12.1
unnamed: R12.2, R13.1
unnamed: R13.2, R14.1
unnamed: R14.2, R15.1
unnamed: R15.2, R16.1
unnamed: R16.2, R17.1
unnamed: R17.2, R18.1
unnamed: R19.2, R20.1
unnamed: R20.2, R21.1
unnamed: R21.2, R22.1
unnamed: R22.2, R23.1
unnamed: R23.2, R24.1
unnamed: R24.2, R25.1
unnamed: R25.2, R26.1
unnamed: R26.2, R27.1
unnamed: R28.2, R29.1
unnamed: R29.2, R30.1
unnamed: R30.2, R31.1
unnamed: R31.2, R32.1
unnamed: R32.2, R33.1
unnamed: R33.2, R34.1
unnamed: R34.2, R35.1
unnamed: R35.2, R36.1
unnamed: R37.2, R38.1
unnamed: R38.2, R39.1
unnamed: R39.2, R40.1
unnamed: R40.2, R41.1
unnamed: R41.2, R42.1
unnamed: R42.2, R43.1
unnamed: R43.2, R44.1
unnamed: R44.2, R45.1
unnamed: R46.2, R47.1
unnamed: R47.2, R48.1
unnamed: R48.2, R49.1
unnamed: R49.2, R50.1
unnamed: R50.2, R51.1
unnamed: R51.2, R52.1
unnamed: R52.2, R53.1
unnamed: R53.2, R54.1
unnamed: R55.2, R56.1
unnamed: R56.2, R57.1
unnamed: R57.2, R58.1
unnamed: R58.2, R59.1
unnamed: R59.2, R60.1
unnamed: R60.2, R61.1
unnamed: R61.2, R62.1
unnamed: R62.2, R63.1
unnamed: R64.2, R65.1
unnamed: R65.2, R66.1
unnamed: R66.2, R67.1
unnamed: R67.2, R68.1
unnamed: R68.2, R69.1
unnamed: R69.2, R70.1
unnamed: R70.2, R71.1
unnamed: R71.2, R72.1
unnamed: R73.2, R74.1
unnamed: R74.2, R75.1
unnamed: R75.2, R76.1
unnamed: R76.2, R77.1
unnamed: R77.2, R78.1
unnamed: R78.2, R79.1
unnamed: R79.2, R80.1
unnamed: R80.2, R81.1
unnamed: R82.2, R83.1
unnamed: R83.2, R84.1
unnamed: R84.2, R85.1
unnamed: R85.2, R86.1
unnamed: R86.2, R87.1
unnamed: R87.2, R88.1
unnamed: R88.2, R89.1
unnamed: R89.2, R90.1
unnamed: R91.2, R92.1
unnamed: R92.2, R93.1
unnamed: R93.2, R94.1
unnamed: R94.2, R95.1
unnamed: R95.2, R96.1
unnamed: R96.2, R97.1
unnamed: R97.2, R98.1
unnamed: R98.2, R99.1
unnamed: R100.2, R101.1
unnamed: R101.2, R102.1
unnamed: R102.2, R103.1
unnamed: R103.2, R104.1
unnamed: R104.2, R105.1
unnamed: R105.2, R106.1
unnamed: R106.2, R107.1
unnamed: R107.2, R108.1
unnamed: R5.2, R113.1
unnamed: R113.2, R114.1
unnamed: R114.2, R115.1
unnamed: R4.2, R6.1, R115.2, R116.1
unnamed: R116.2, R117.1
unnamed: R117.2, R118.1
unnamed: R118.2, R119.1

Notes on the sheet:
INPUT: 27.1mA MAX 23.6mA NOM 15.7mA MIN
GPIO GND
OUTPUT: PHOTOVOLTAIC (IGNORE GRAPHIC) 14uA@8V
V_GPIO = 0V: FET Q1 OFF V_GPIO = 5V: FET Q1 ON
INTERNAL LED ^^^ ACTUALLY UNIPOLAR (IGNORE GRAPHIC)
IPD70R360P7SAUMA1
HVDC+ HVDC-
TOUCHING ANYTHING OUTSIDE THIS BOX COULD KILL YOU
ANYTHING INSIDE THIS BOX IS SAFE TO TOUCH
HVDC+ HVDC+
HVDC_NEG_SWITCHED HVDC_NEG_SWITCHED

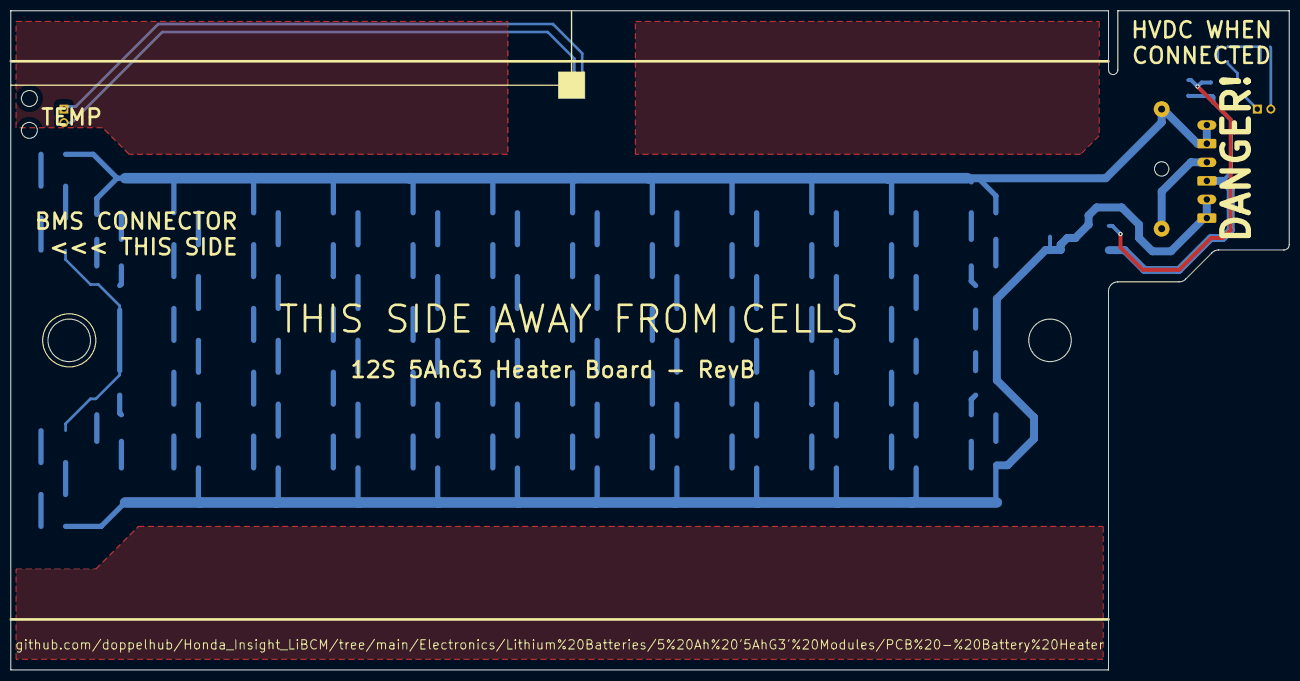
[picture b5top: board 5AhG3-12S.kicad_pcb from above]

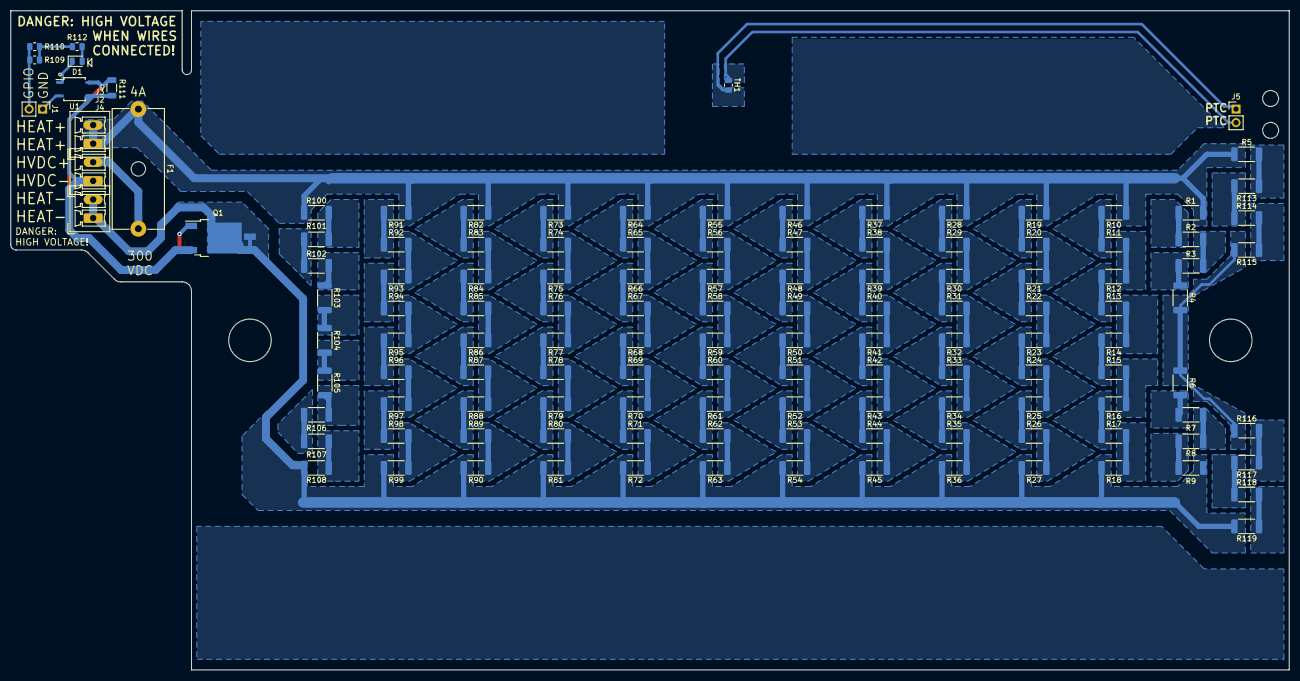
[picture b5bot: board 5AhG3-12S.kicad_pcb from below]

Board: 2 copper layers, 240.5 x 124.0 mm, 129 parts (129 on the bottom side), 113 nets.

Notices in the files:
Firmware/firmwareLiBCM/src/gpio.cpp:
Copyright 2021-2024(c) John Sullivan
